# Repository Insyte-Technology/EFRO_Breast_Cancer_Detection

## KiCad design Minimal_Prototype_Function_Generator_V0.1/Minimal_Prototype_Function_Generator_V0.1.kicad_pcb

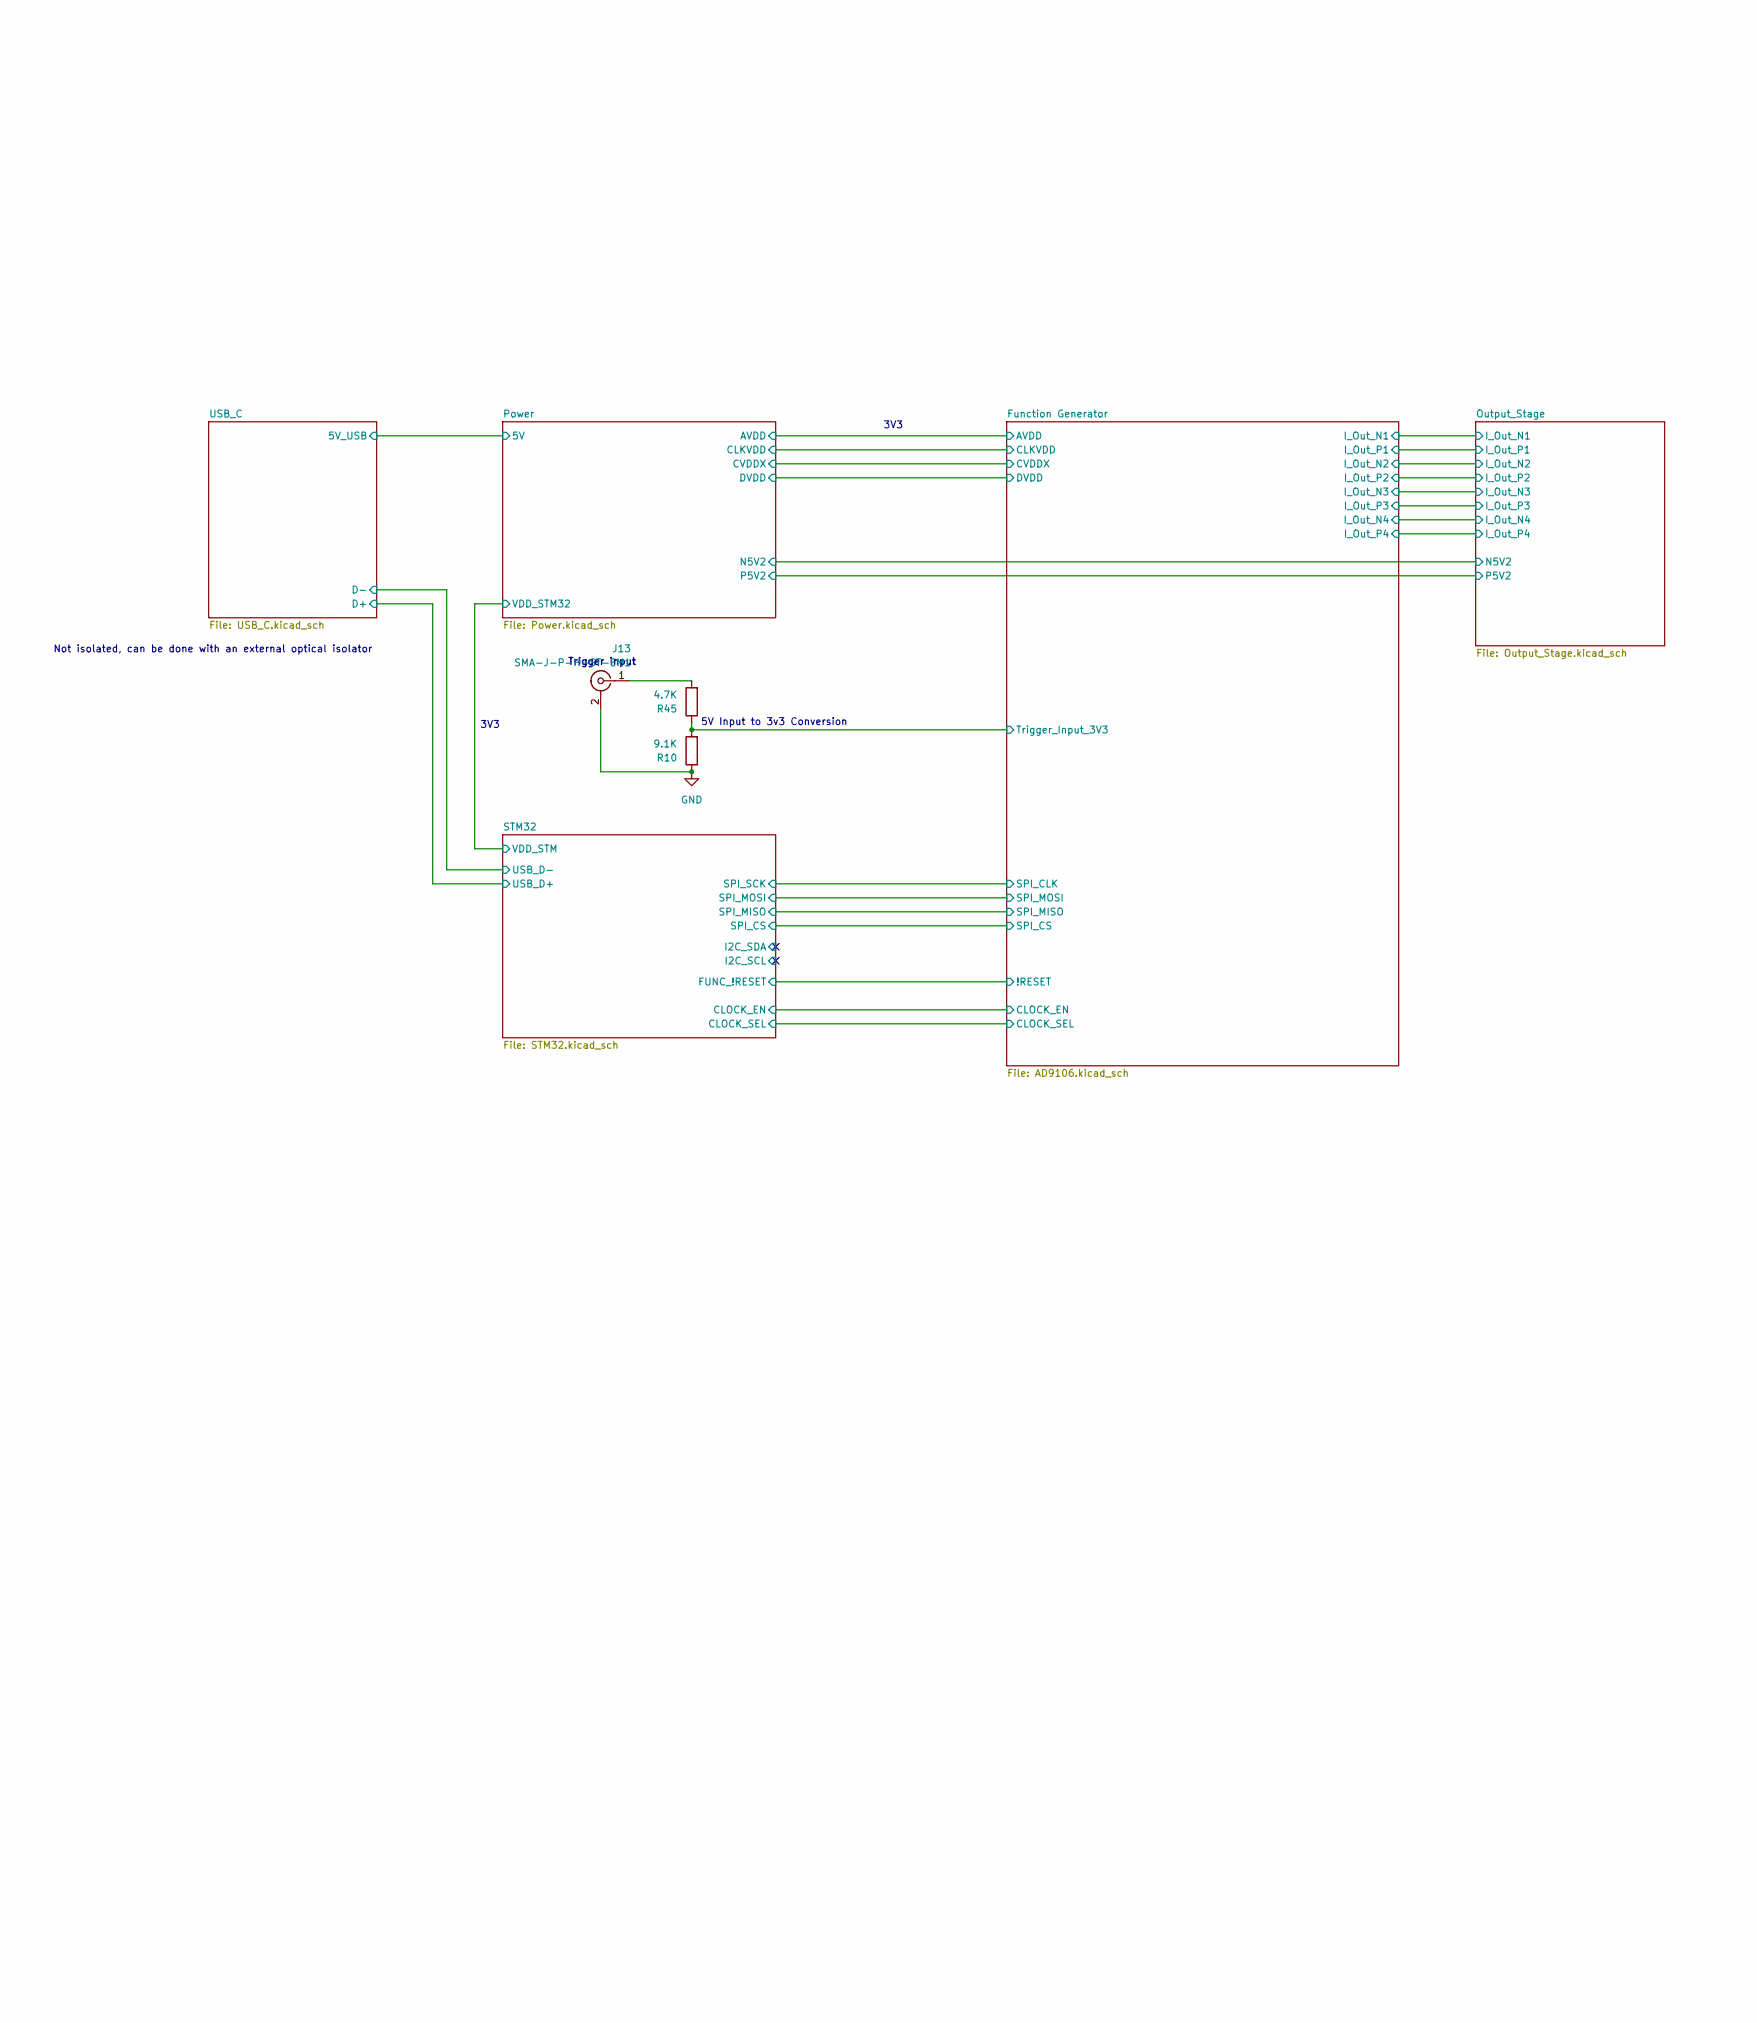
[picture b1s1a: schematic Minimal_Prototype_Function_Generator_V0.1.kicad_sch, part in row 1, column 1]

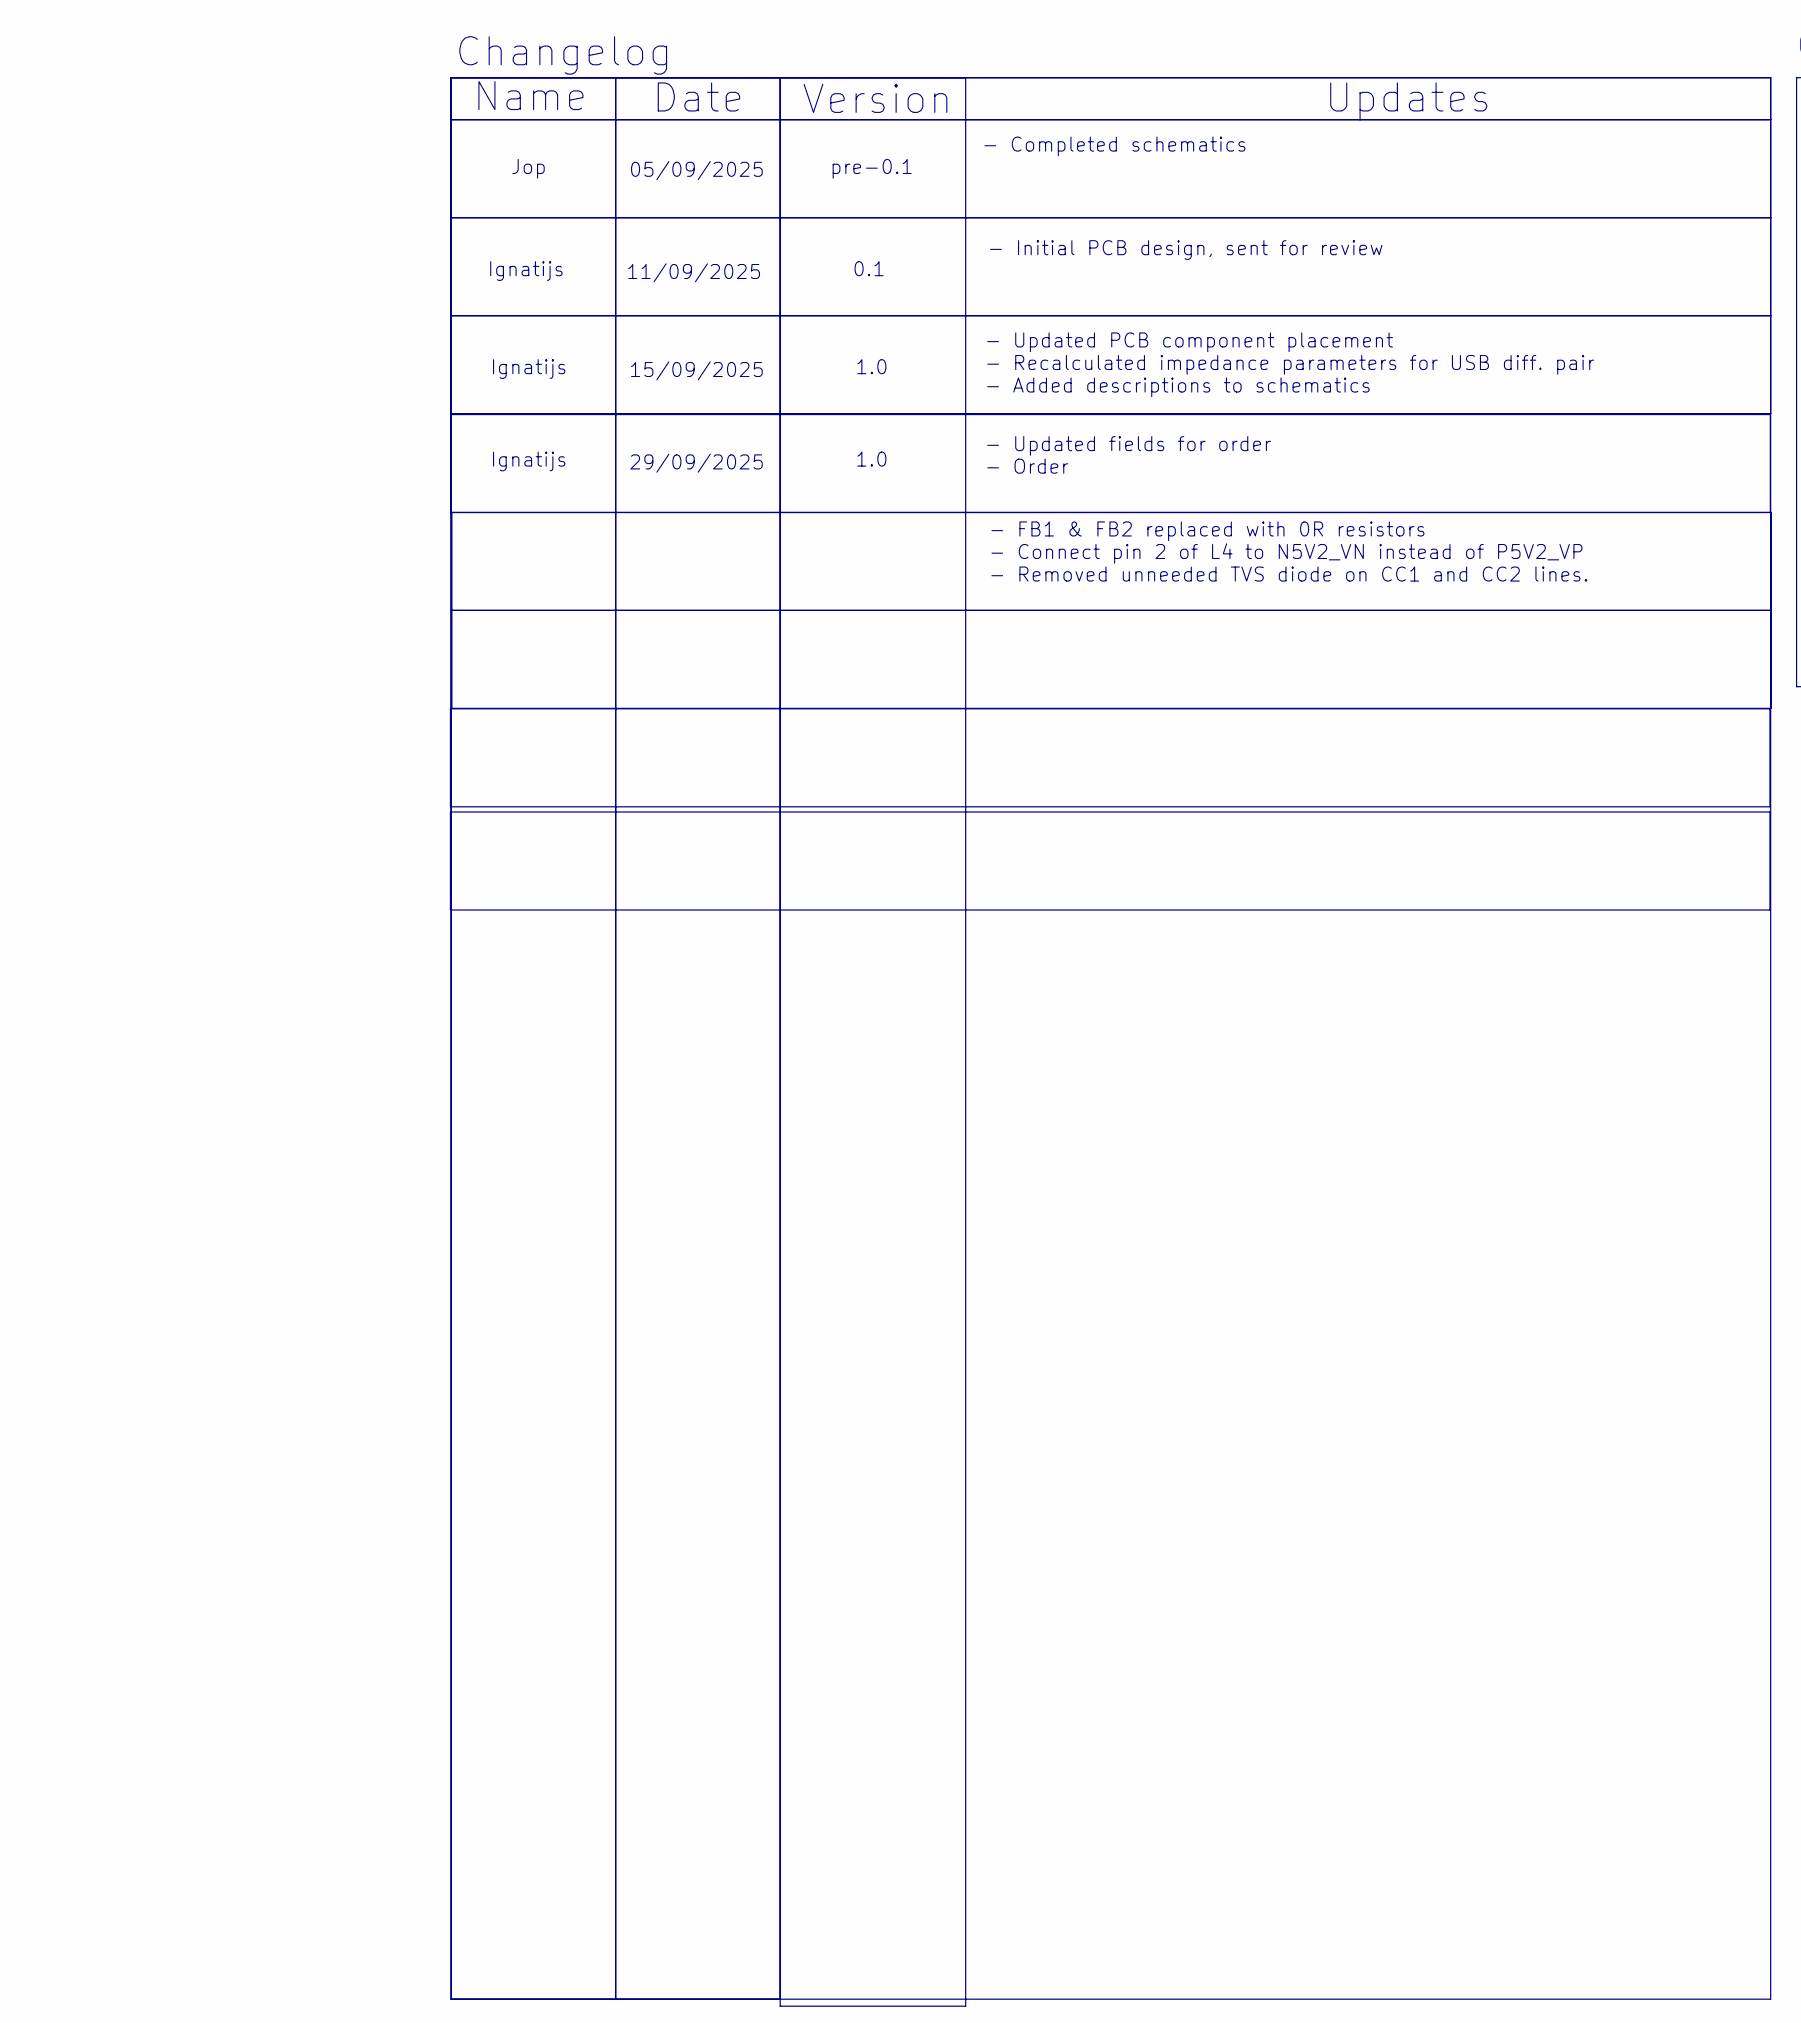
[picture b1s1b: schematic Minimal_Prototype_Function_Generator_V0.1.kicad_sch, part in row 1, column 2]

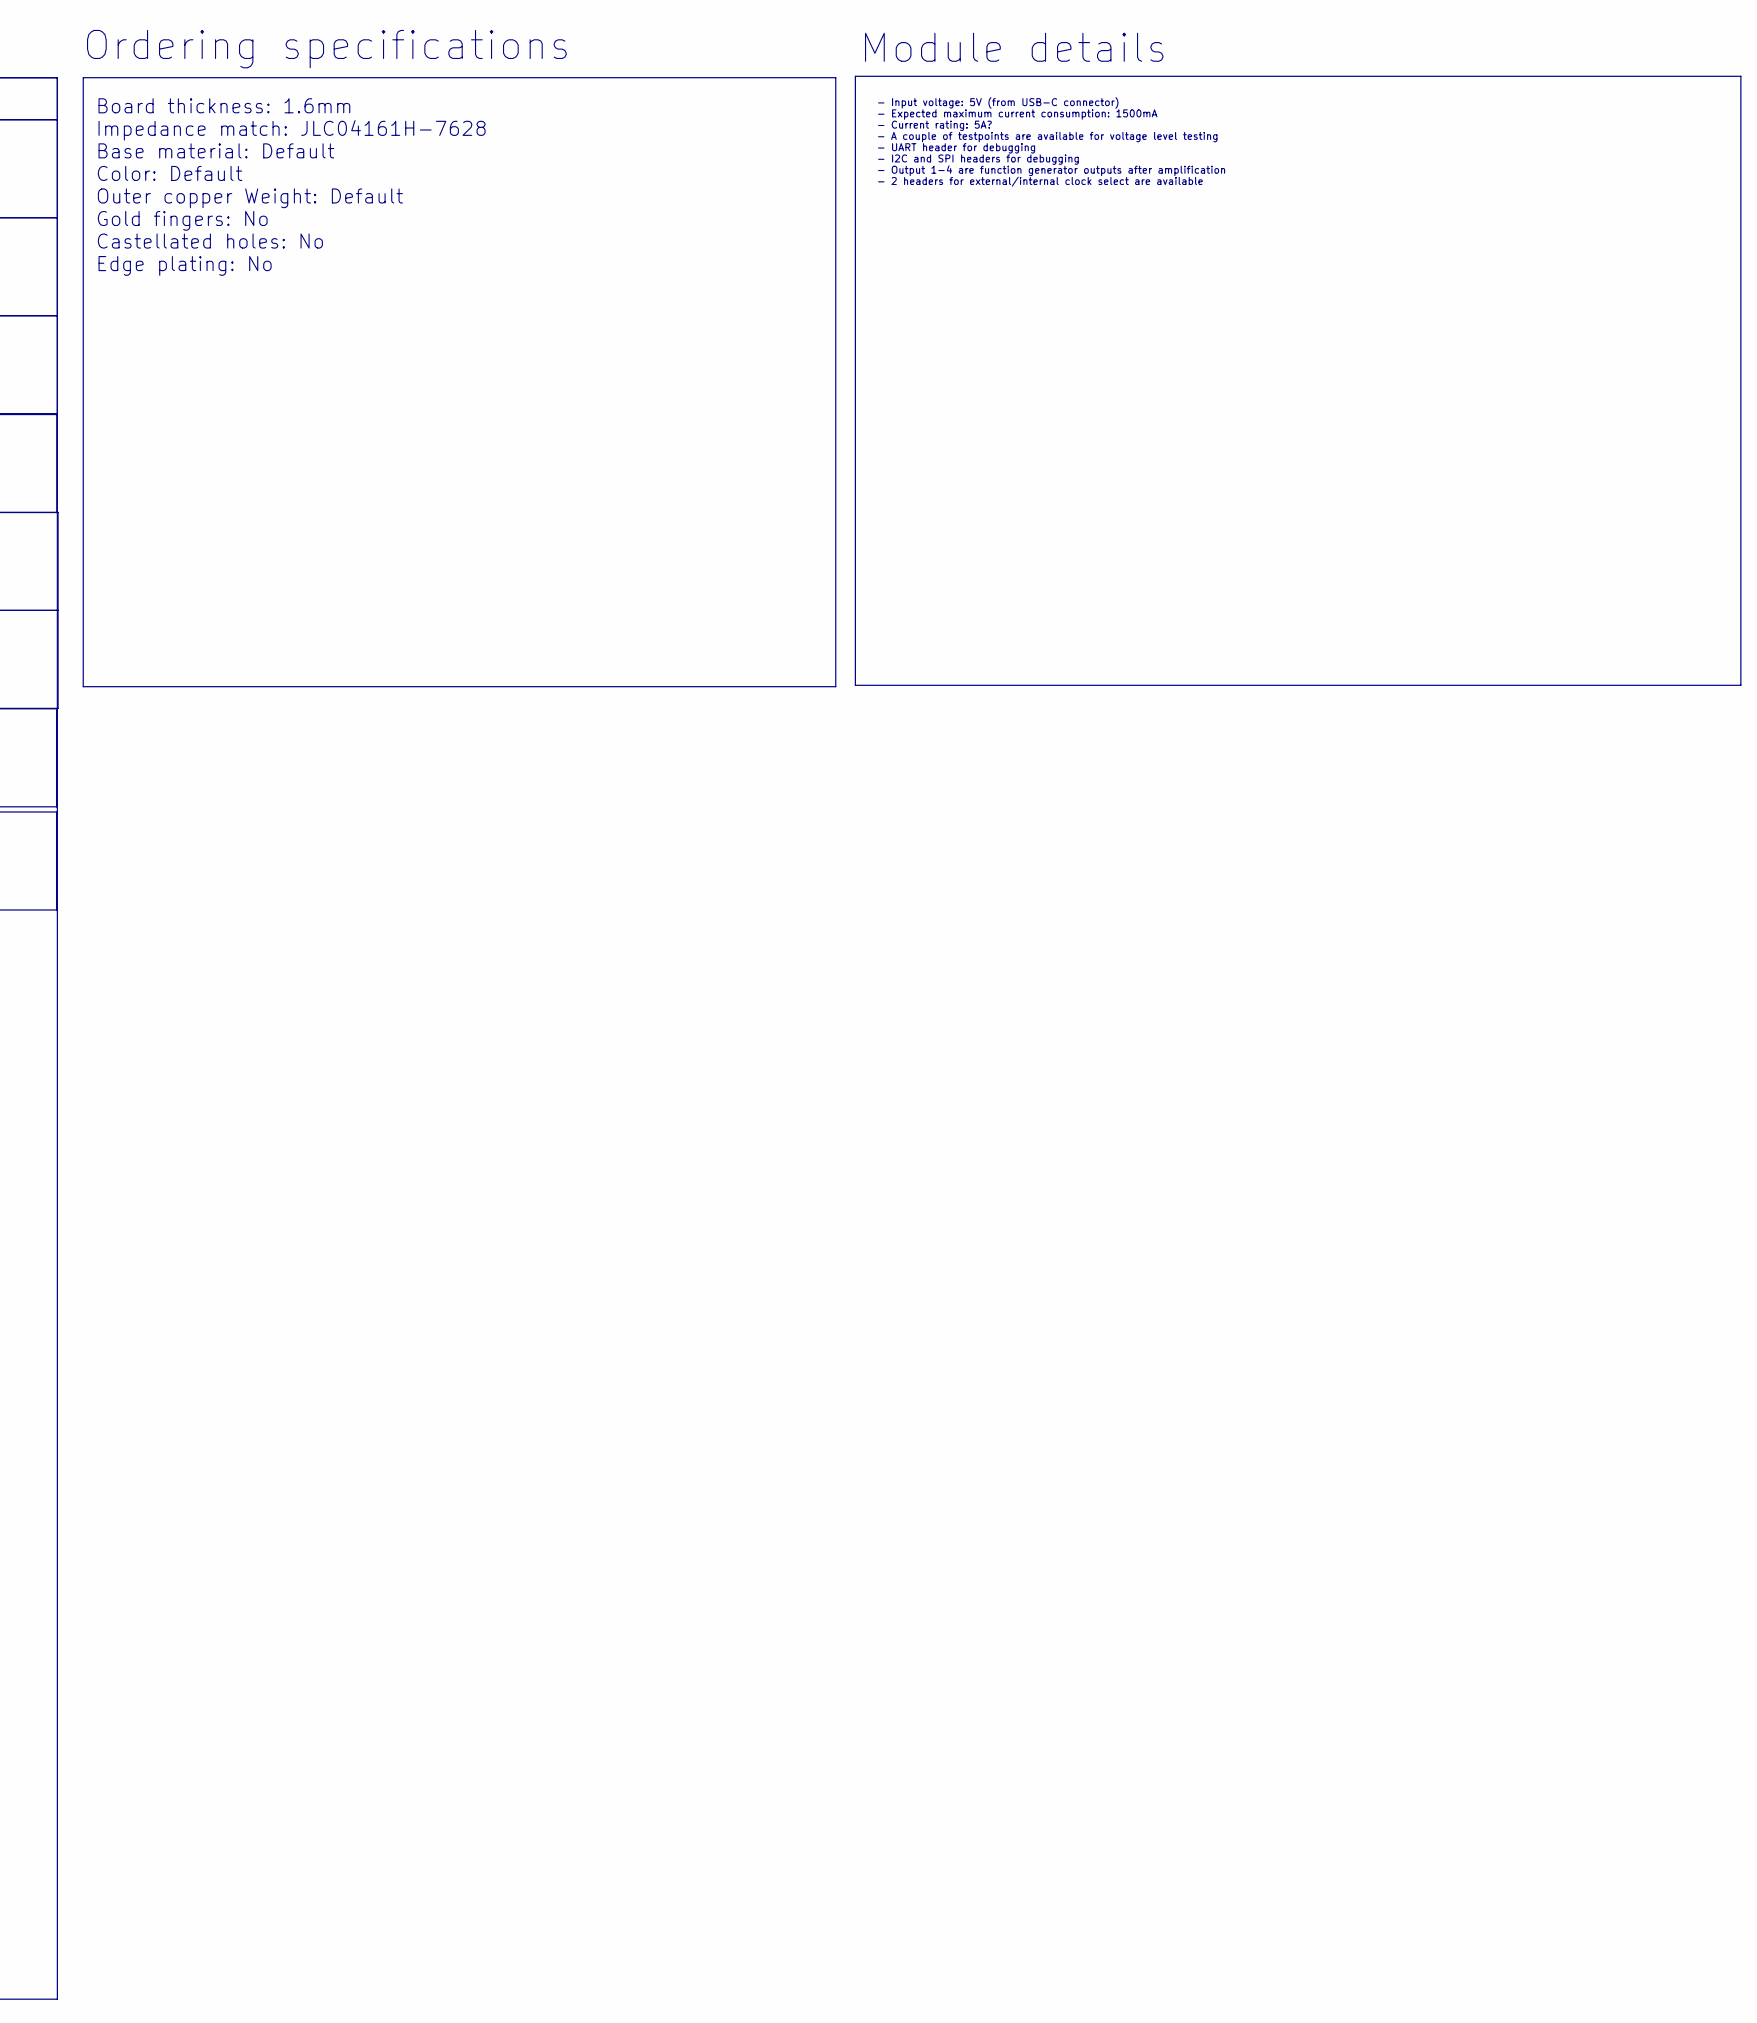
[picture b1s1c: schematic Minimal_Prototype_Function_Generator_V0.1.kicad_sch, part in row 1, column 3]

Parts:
J13: SMA-J-P-H-ST-EM1; 142-0701-851; Mouser Part Number 530-142-0701-801
R10: 9.1K; R_0603
R45: 4.7K; R_0603

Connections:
/Function Generator/Trigger_Input_3V3: R10.2, R45.1; also elsewhere on the board
GND: J13.2, J13.3 (Ext_3), R10.1; also elsewhere on the board
unnamed: J13.1, R45.2

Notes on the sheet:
Ignatijs
1.0
- Updated PCB component placement - Recalculated impedance parameters for USB diff. pair - Added descriptions to schematics
- Input voltage: 5V (from USB-C connector) - Expected maximum current consumption: 1500mA - Current rating: 5A? - A couple of testpoints are available for voltage level testing - UART header for debugging - I2C and SPI headers for debugging - Output 1-4 are function generator outputs after amplific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
05/09/2025
pre-0.1
3V3
11/09/2025
Updates
- Completed schematics
- Initial PCB design, sent for review
- FB1 & FB2 replaced with 0R resistors - Connect pin 2 of L4 to N5V2_VN instead of P5V2_VP - Removed unneeded TVS diode on CC1 and CC2 lines.
Ordering specifications
Module details
- Updated fields for order - Order
29/09/2025
Trigger input
Changelog
Version
5V Input to 3v3 Conversion
0.1
15/09/2025
Date
Jop
Name
Not isolated, can be done with an external optical isolator
Board thickness: 1.6mm Impedance match: JLC04161H-7628 Base material: Default Color: Default Outer copper Weight: Default Gold fingers: No Castellated holes: No Edge plating: No

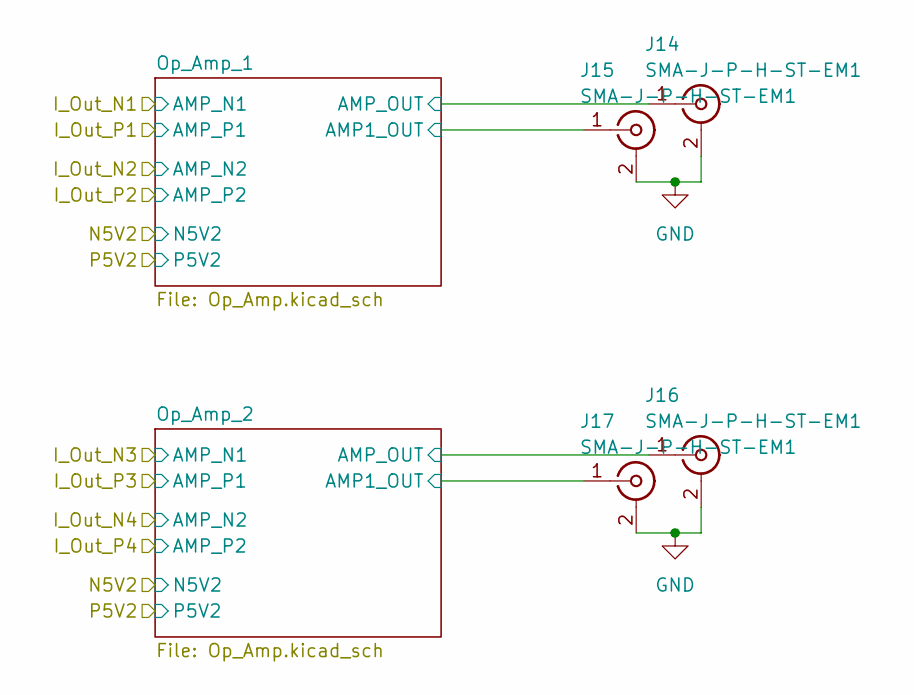
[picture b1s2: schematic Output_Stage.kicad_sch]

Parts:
J14, J15, J16, J17: SMA-J-P-H-ST-EM1; 142-0701-851; Mouser Part Number 530-142-0701-801

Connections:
/Output_Stage/Op_Amp_1/AMP1_OUT: J15.1; also elsewhere on the board
/Output_Stage/Op_Amp_1/AMP_OUT: J14.1; also elsewhere on the board
/Output_Stage/Op_Amp_2/AMP1_OUT: J17.1; also elsewhere on the board
/Output_Stage/Op_Amp_2/AMP_OUT: J16.1; also elsewhere on the board
GND: J14.2, J14.3 (Ext_3), J15.2, J15.3 (Ext_3), J16.2, J16.3 (Ext_3), J17.2, J17.3 (Ext_3); also elsewhere on the board

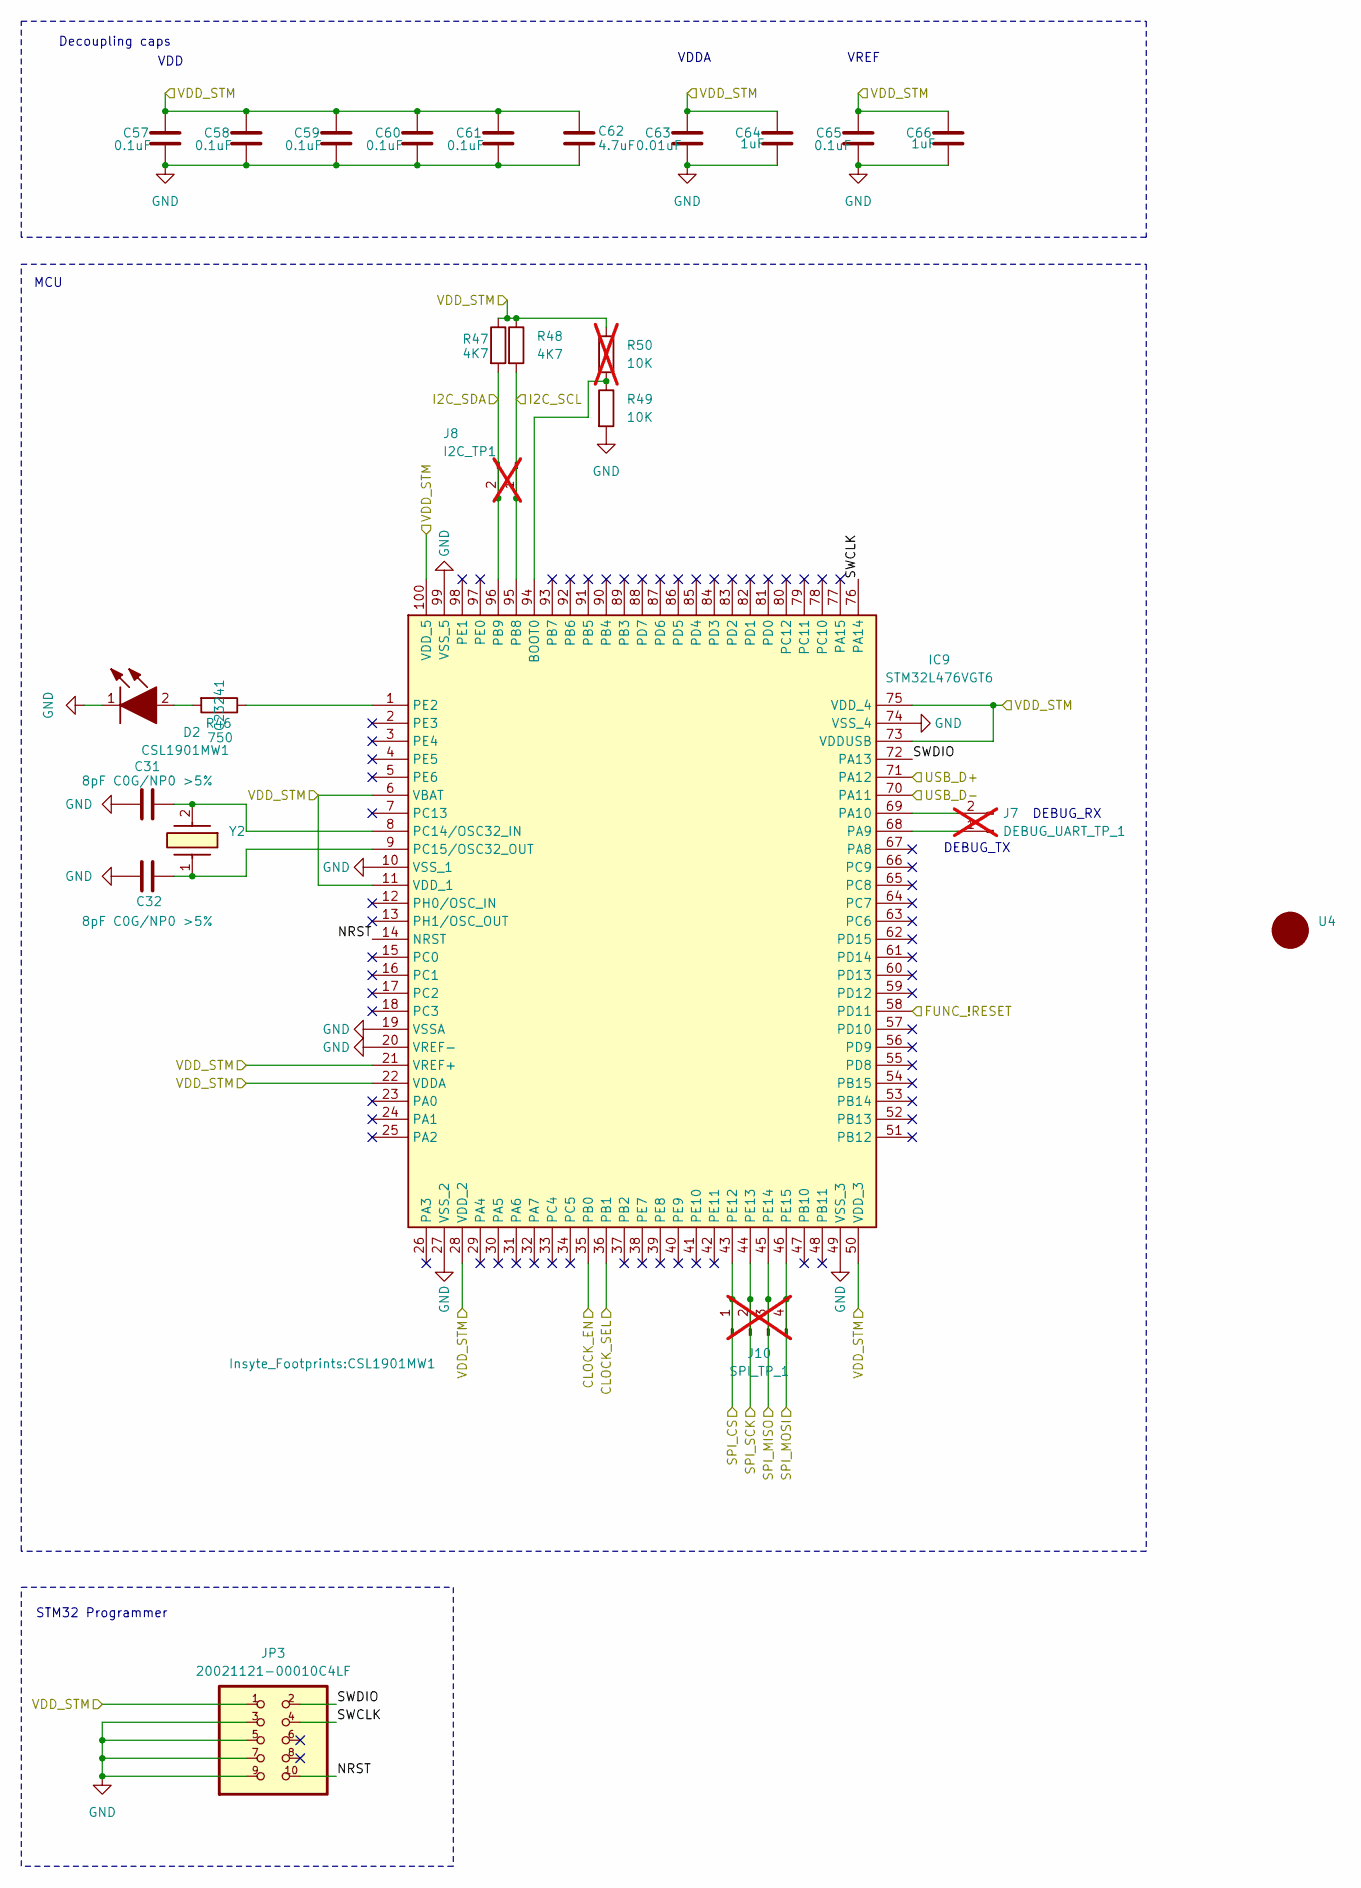
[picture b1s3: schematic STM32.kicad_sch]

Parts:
C31, C32: 8pF C0G/NP0 >5%; C_0603; LCSC Part # C36508
C57, C58, C59, C60, C61, C65: 0.1uF; C_0603; voltage rating 16V; LCSC Part # C14663
C62: 4.7uF; C_0603; voltage rating 16V; LCSC Part # C19702
C63: 0.01uF; C_0603; voltage rating 16V; LCSC Part # C1589
C64, C66: 1uF; C_0603; voltage rating 16V; LCSC Part # C15849
D2: CSL1901MW1; Mouser Part Number 755-CSL1901MW1
IC9: STM32L476VGT6; QFP50P1600X1600X160-100N; Mouser Part Number 511-STM32L476VGT6
J7: DEBUG_UART_TP_1; PinHeader_1x02_P2.54mm_Vertical; not fitted
J8: I2C_TP1; PinHeader_1x02_P2.54mm_Vertical; not fitted
J10: SPI_TP_1; PinHeader_1x04_P2.54mm_Vertical; not fitted
JP3: 20021121-00010C4LF; 2002112100010C4LF; LCSC Part # C150517
R46: 750; R_0603; LCSC Part # C23241
R47, R48: 4K7; R_0603; LCSC Part # C23162
R49: 10K; R_0603
R50: 10K; R_0603; not fitted
U4: 15x6_Insyte_Logo
Y2: ECS-.327-7-16-C-TR; ECS327516TR; Mouser Part Number 520-.327-7-16-CT

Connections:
/Function Generator/!RESET: IC9.58 (PD11); also elsewhere on the board
/Function Generator/CLOCK_EN: IC9.35 (PB0); also elsewhere on the board
/Function Generator/CLOCK_SEL: IC9.36 (PB1); also elsewhere on the board
/Function Generator/SPI_CLK: IC9.44 (PE13), J10.2; also elsewhere on the board
/Function Generator/SPI_CS: IC9.43 (PE12), J10.1; also elsewhere on the board
/Function Generator/SPI_MISO: IC9.45 (PE14), J10.3; also elsewhere on the board
/Function Generator/SPI_MOSI: IC9.46 (PE15), J10.4; also elsewhere on the board
/Power/VDD_STM32: C57.1, C58.1, C59.1, C60.1, C61.1, C62.1, C63.1, C64.1, C65.1, C66.1, IC9.6 (VBAT), IC9.11 (VDD_1), IC9.21 (VREF+), IC9.22 (VDDA), IC9.28 (VDD_2), IC9.50 (VDD_3), IC9.73 (VDDUSB), IC9.75 (VDD_4), IC9.100 (VDD_5), JP3.1, R47.1, R48.1, R50.1; also elsewhere on the board
/STM32/I2C_SCL: IC9.95 (PB8), J8.1, R48.2
/STM32/I2C_SDA: IC9.96 (PB9), J8.2, R47.2
/STM32/NRST: IC9.14 (NRST), JP3.10
/STM32/SWCLK: IC9.76 (PA14), JP3.4
/STM32/SWDIO: IC9.72 (PA13), JP3.2
/USB_C/D+: IC9.71 (PA12); also elsewhere on the board
/USB_C/D-: IC9.70 (PA11); also elsewhere on the board
GND: C31.1, C32.1, C57.2, C58.2, C59.2, C60.2, C61.2, C62.2, C63.2, C64.2, C65.2, C66.2, D2.1 (K), IC9.10 (VSS_1), IC9.19 (VSSA), IC9.20 (VREF-), IC9.27 (VSS_2), IC9.49 (VSS_3), IC9.74 (VSS_4), IC9.99 (VSS_5), JP3.3, JP3.5, JP3.7, JP3.9, R49.2; also elsewhere on the board
unnamed: D2.2 (A), R46.2
unnamed: IC9.94 (BOOT0), R49.1, R50.2
unnamed: IC9.68 (PA9), J7.1
unnamed: IC9.69 (PA10), J7.2
unnamed: C31.2, IC9.8 (PC14/OSC32_IN), Y2.2 (OUT/IN_2)
unnamed: C32.2, IC9.9 (PC15/OSC32_OUT), Y2.1
unnamed: IC9.1 (PE2), R46.1

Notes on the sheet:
STM32 Programmer
VREF
MCU
VDD
VDDA
Decoupling caps
DEBUG_RX
DEBUG_TX

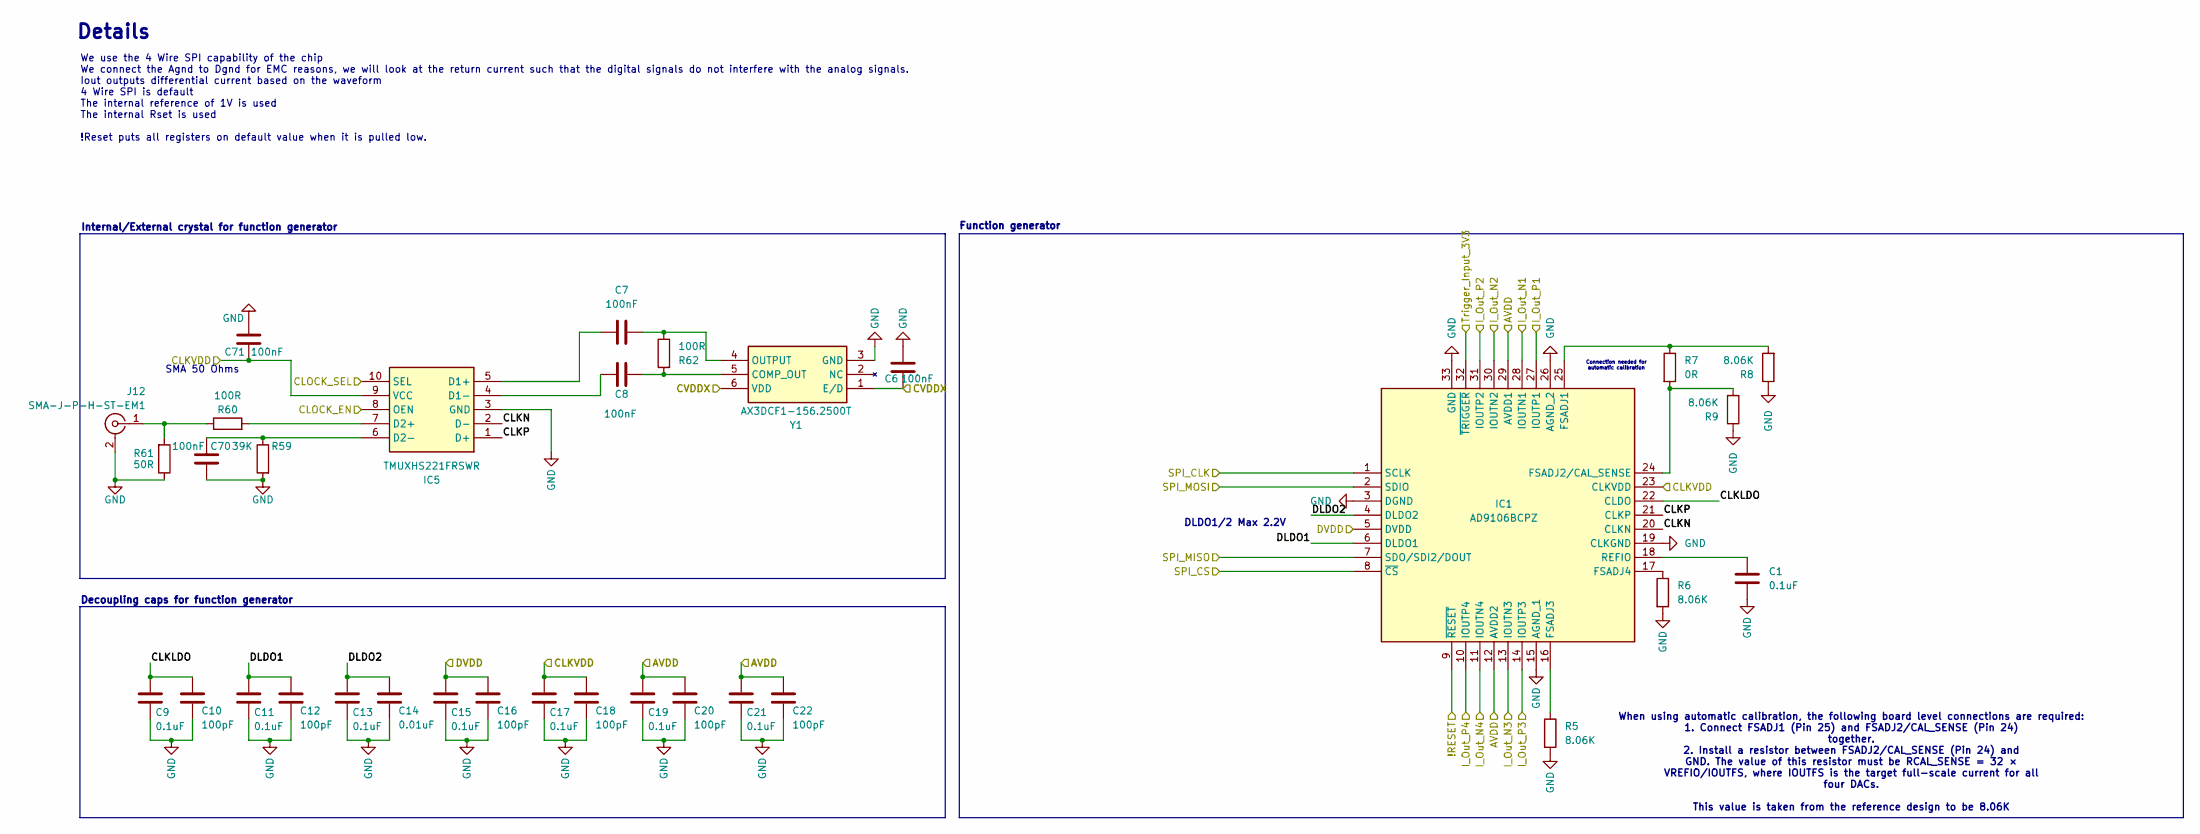
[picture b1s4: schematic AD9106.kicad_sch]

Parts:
C1, C9, C17: 0.1uF; C_0402
C6, C7, C8, C70, C71: 100nF; C_0603
C10, C18: 100pF; C_0402
C11, C13, C15, C19, C21: 0.1uF; C_0603
C12, C16, C20, C22: 100pF; C_0603
C14: 0.01uF; C_0603
IC1: AD9106BCPZ; QFN50P500X500X80-33N-D; Mouser Part Number 584-AD9106BCPZ
IC5: TMUXHS221FRSWR; Manufacturer_Part_Number TMUXHS221FRSWR
J12: SMA-J-P-H-ST-EM1; 142-0701-851; Mouser Part Number 530-142-0701-801
R5, R6, R8, R9: 8.06K; R_0603
R7: 0R; R_0603
R59: 39K; R_0603
R60, R62: 100R; R_0603
R61: 50R; R_0603
Y1: AX3DCF1-156.2500T; AX3_3.2x2.5; Mouser Part Number 815-AX3DCF1156.2500T

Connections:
/Function Generator/!RESET: IC1.9 (~RESET); also elsewhere on the board
/Function Generator/AVDD: C19.1, C20.1, C21.1, C22.1, IC1.12 (AVDD2), IC1.29 (AVDD1); also elsewhere on the board
/Function Generator/CLKLDO: C9.1, C10.1, IC1.22 (CLDO)
/Function Generator/CLKN: IC1.20 (CLKN), IC5.2 (D-)
/Function Generator/CLKP: IC1.21 (CLKP), IC5.1 (D+)
/Function Generator/CLKVDD: C17.1, C18.1, C71.2, IC1.23 (CLKVDD), IC5.9 (VCC); also elsewhere on the board
/Function Generator/CLOCK_EN: IC5.8 (OEN); also elsewhere on the board
/Function Generator/CLOCK_SEL: IC5.10 (SEL); also elsewhere on the board
/Function Generator/CVDDX: C6.1, Y1.1 (E/D), Y1.6 (VDD); also elsewhere on the board
/Function Generator/DLDO1: C11.1, C12.1, IC1.6 (DLDO1)
/Function Generator/DLDO2: C13.1, C14.1, IC1.4 (DLDO2)
/Function Generator/DVDD: C15.1, C16.1, IC1.5 (DVDD); also elsewhere on the board
/Function Generator/I_Out_N1: IC1.28 (IOUTN1); also elsewhere on the board
/Function Generator/I_Out_N2: IC1.30 (IOUTN2); also elsewhere on the board
/Function Generator/I_Out_N3: IC1.13 (IOUTN3); also elsewhere on the board
/Function Generator/I_Out_N4: IC1.11 (IOUTN4); also elsewhere on the board
/Function Generator/I_Out_P1: IC1.27 (IOUTP1); also elsewhere on the board
/Function Generator/I_Out_P2: IC1.31 (IOUTP2); also elsewhere on the board
/Function Generator/I_Out_P3: IC1.14 (IOUTP3); also elsewhere on the board
/Function Generator/I_Out_P4: IC1.10 (IOUTP4); also elsewhere on the board
/Function Generator/SPI_CLK: IC1.1 (SCLK); also elsewhere on the board
/Function Generator/SPI_CS: IC1.8 (~CS); also elsewhere on the board
/Function Generator/SPI_MISO: IC1.7 (SDO/SDI2/DOUT); also elsewhere on the board
/Function Generator/SPI_MOSI: IC1.2 (SDIO); also elsewhere on the board
/Function Generator/Trigger_Input_3V3: IC1.32 (~TRIGGER); also elsewhere on the board
GND: C1.2, C6.2, C9.2, C10.2, C11.2, C12.2, C13.2, C14.2, C15.2, C16.2, C17.2, C18.2, C19.2, C20.2, C21.2, C22.2, C70.1, C71.1, IC1.3 (DGND), IC1.15 (AGND_1), IC1.19 (CLKGND), IC1.26 (AGND_2), IC1.33 (GND), IC5.3 (GND), J12.2, J12.3 (Ext_3), R5.2, R6.2, R8.1, R9.1, R59.2, R61.1, Y1.3 (GND); also elsewhere on the board
unnamed: IC1.25 (FSADJ1), R7.1, R8.2
unnamed: IC1.24 (FSADJ2/CAL_SENSE), R7.2, R9.2
unnamed: IC1.16 (FSADJ3), R5.1
unnamed: IC1.17 (FSADJ4), R6.1
unnamed: C1.1, IC1.18 (REFIO)
unnamed: C7.2, IC5.5 (D1+)
unnamed: C8.2, IC5.4 (D1-)
unnamed: IC5.7 (D2+), R60.2
unnamed: C70.2, IC5.6 (D2-), R59.1
unnamed: J12.1, R60.1, R61.2
unnamed: C8.1, R62.2, Y1.5 (COMP_OUT)
unnamed: C7.1, R62.1, Y1.4 (OUTPUT)

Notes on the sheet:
DLDO1/2 Max 2.2V
SMA 50 Ohms
Function generator
Details
Connection needed for automatic calibration
Internal/External crystal for function generator
We use the 4 Wire SPI capability of the chip We connect the Agnd to Dgnd for EMC reasons, we will look at the return current such that the digital signals do not interfere with the analog signals. Iout outputs differential current based on the waveform 4 Wire SPI is default The internal reference o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
When using automatic calibration, the following board level connections are required: 1. Connect FSADJ1 (Pin 25) and FSADJ2/CAL_SENSE (Pin 24) together. 2. Install a resistor between FSADJ2/CAL_SENSE (Pin 24) and GND. The value of this resistor must be RCAL_SENSE = 32 × VREFIO/IOUTFS, where IOUTFS 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
Decoupling caps for function generator

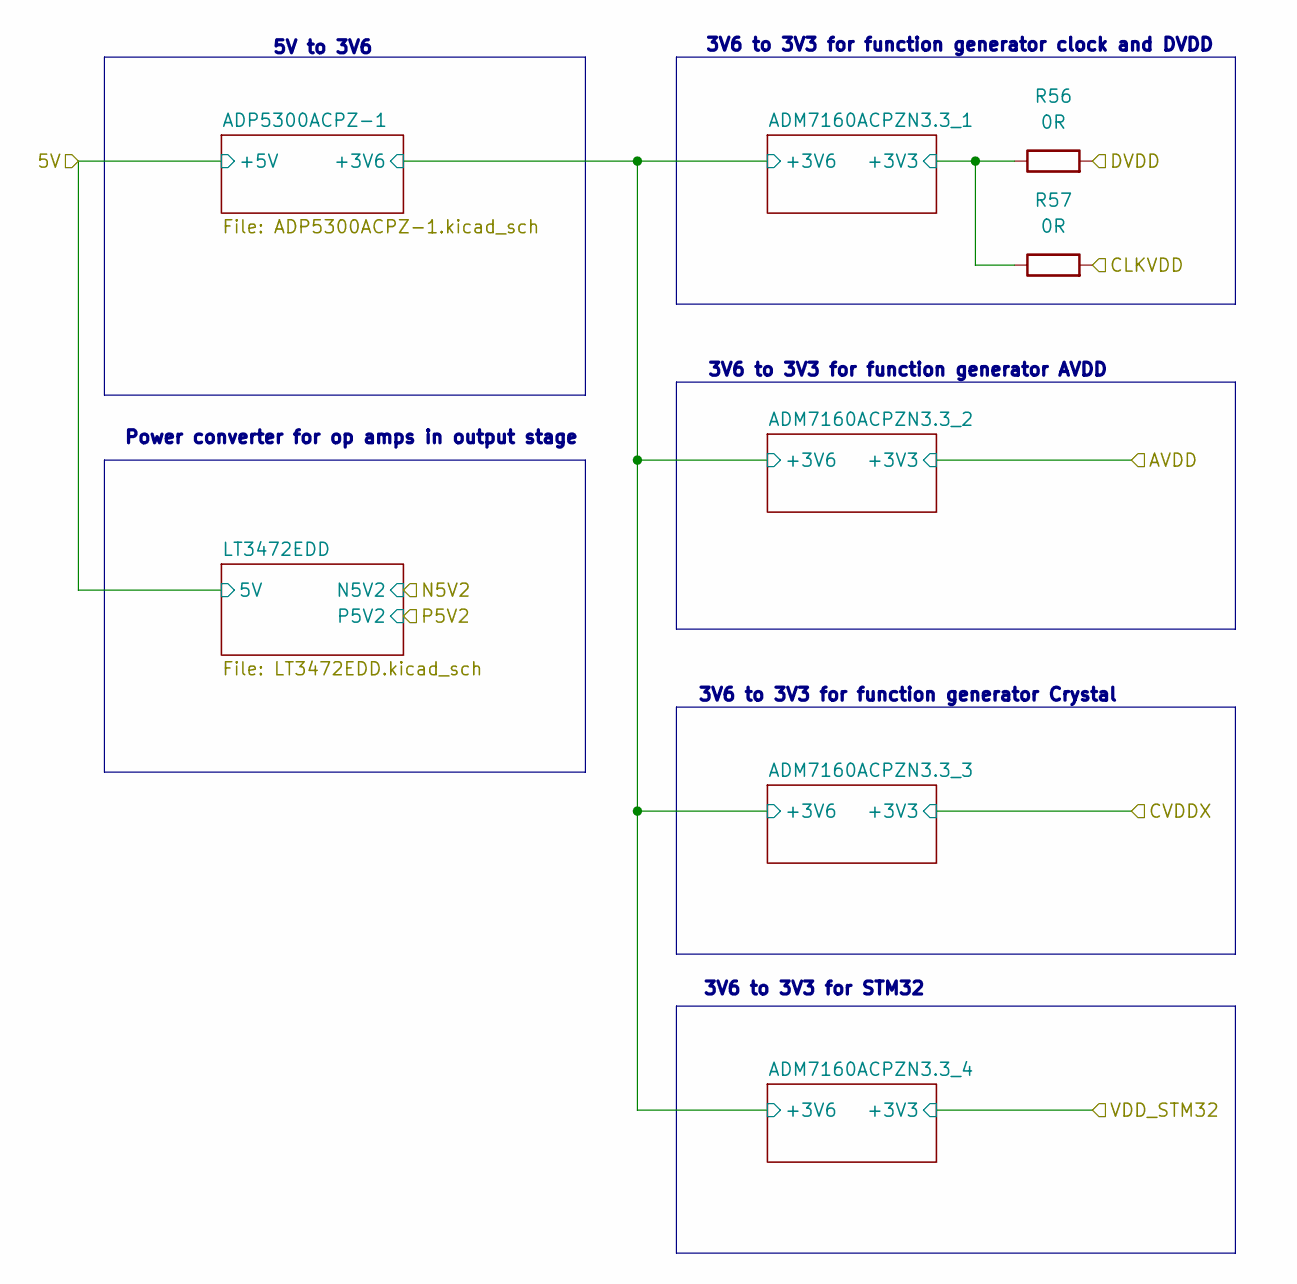
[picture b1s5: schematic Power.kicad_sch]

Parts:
R56, R57: 0R; R_0603

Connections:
/Function Generator/CLKVDD: R57.2; also elsewhere on the board
/Function Generator/DVDD: R56.2; also elsewhere on the board
/Power/ADM7160ACPZN3.3_1/+3V3: R56.1, R57.1; also elsewhere on the board

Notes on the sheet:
3V6 to 3V3 for function generator clock and DVDD
3V6 to 3V3 for function generator AVDD
3V6 to 3V3 for STM32
3V6 to 3V3 for function generator Crystal
Power converter for op amps in output stage
5V to 3V6
